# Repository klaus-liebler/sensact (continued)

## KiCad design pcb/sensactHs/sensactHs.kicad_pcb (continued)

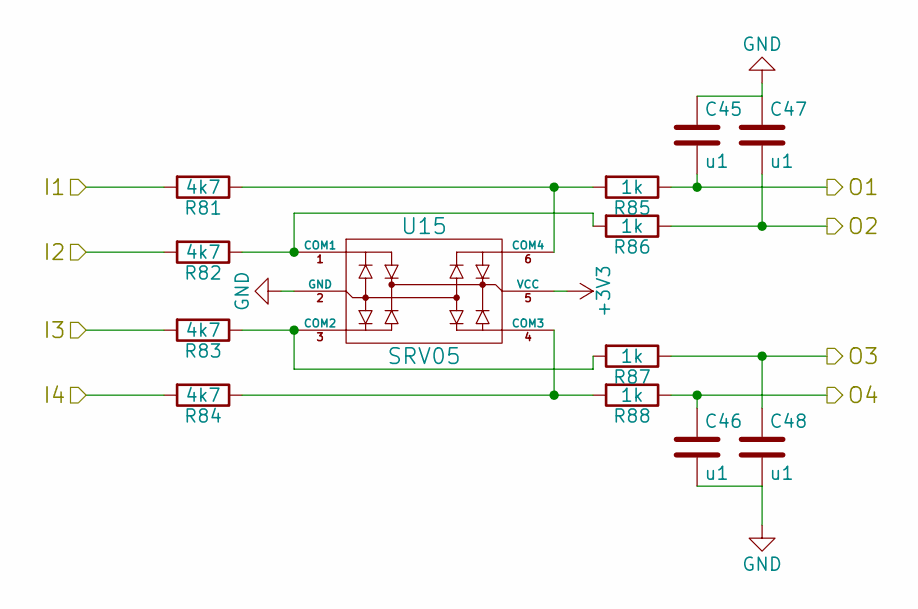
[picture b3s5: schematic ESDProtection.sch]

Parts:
C5, C6, C7, C8: u1; C_0805_HandSoldering
R1, R2, R3, R4: 4k7; R_0805_HandSoldering
R5, R6, R7, R8: 1k; R_0805_HandSoldering
U5: SRV05; SOT-23-6_handsolder

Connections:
/01 input/ESDProtection1/I1: R1.2; also elsewhere on the board
/01 input/ESDProtection1/I2: R2.2; also elsewhere on the board
/01 input/ESDProtection1/I3: R3.2; also elsewhere on the board
/01 input/ESDProtection1/I4: R4.2; also elsewhere on the board
/01 input/ESDProtection1/O1: C5.2, R5.1; also elsewhere on the board
/01 input/ESDProtection1/O2: C7.2, R6.1; also elsewhere on the board
/01 input/ESDProtection1/O3: C8.1, R7.1; also elsewhere on the board
/01 input/ESDProtection1/O4: C6.1, R8.1; also elsewhere on the board
GND: C5.1, C6.2, C7.1, C8.2, U5.2 (GND); also elsewhere on the board
unnamed: R1.1, R5.2, U5.6 (COM4)
unnamed: R2.1, R6.2, U5.1 (COM1)
unnamed: R3.1, R7.2, U5.3 (COM2)
unnamed: R4.1, R8.2, U5.4 (COM3)

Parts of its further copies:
C9, C10, C11, C12, C13, C14, C15, C16, C17, C18, C19, C20, C21, C22, C23, C24, C25, C26, C27, C28, C29, C30, C31, C32, C33, C34, C35, C36, C37, C38, C39, C40, C41, C42, C43, C44, C45, C46, C47, C48, C49, C50, C51, C52, C53, C54, C55, C56, C57, C58, C59, C60, C61, C62, C63, C64, C65, C66, C67, C68: u1; C_0805_HandSoldering
R9, R10, R11, R12, R17, R18, R19, R20, R25, R26, R27, R28, R33, R34, R35, R36, R41, R42, R43, R44, R49, R50, R51, R52, R57, R58, R59, R60, R65, R66, R67, R68, R73, R74, R75, R76, R81, R82, R83, R84, R89, R90, R91, R92, R97, R98, R99, R100, R105, R106, R107, R108, R113, R114, R115, R116, R121, R122, R123, R124: 4k7; R_0805_HandSoldering
R13, R14, R15, R16, R21, R22, R23, R24, R29, R30, R31, R32, R37, R38, R39, R40, R45, R46, R47, R48, R53, R54, R55, R56, R61, R62, R63, R64, R69, R70, R71, R72, R77, R78, R79, R80, R85, R86, R87, R88, R93, R94, R95, R96, R101, R102, R103, R104, R109, R110, R111, R112, R117, R118, R119, R120, R125, R126, R127, R128: 1k; R_0805_HandSoldering
U6, U7, U8, U9, U10, U11, U12, U13, U14, U15, U16, U17, U18, U19, U20: SRV05; SOT-23-6_handsolder

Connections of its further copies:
/01 input/ESDProtection2/I1: R9.2; also elsewhere on the board
/01 input/ESDProtection2/I2: R10.2; also elsewhere on the board
/01 input/ESDProtection2/I3: R11.2; also elsewhere on the board
/01 input/ESDProtection2/I4: R12.2; also elsewhere on the board
/01 input/ESDProtection2/O1: C9.2, R13.1; also elsewhere on the board
/01 input/ESDProtection2/O2: C11.2, R14.1; also elsewhere on the board
/01 input/ESDProtection2/O3: C12.1, R15.1; also elsewhere on the board
/01 input/ESDProtection2/O4: C10.1, R16.1; also elsewhere on the board
/01 input/ESDProtection3/I1: R17.2; also elsewhere on the board
/01 input/ESDProtection3/I2: R18.2; also elsewhere on the board
/01 input/ESDProtection3/I3: R19.2; also elsewhere on the board
/01 input/ESDProtection3/I4: R20.2; also elsewhere on the board
/01 input/ESDProtection3/O1: C13.2, R21.1; also elsewhere on the board
/01 input/ESDProtection3/O2: C15.2, R22.1; also elsewhere on the board
/01 input/ESDProtection3/O3: C16.1, R23.1; also elsewhere on the board
/01 input/ESDProtection3/O4: C14.1, R24.1; also elsewhere on the board
/01 input/ESDProtection4/I1: R25.2; also elsewhere on the board
/01 input/ESDProtection4/I2: R26.2; also elsewhere on the board
/01 input/ESDProtection4/I3: R27.2; also elsewhere on the board
/01 input/ESDProtection4/I4: R28.2; also elsewhere on the board
/01 input/ESDProtection4/O1: C17.2, R29.1; also elsewhere on the board
/01 input/ESDProtection4/O2: C19.2, R30.1; also elsewhere on the board
/01 input/ESDProtection4/O3: C20.1, R31.1; also elsewhere on the board
/01 input/ESDProtection4/O4: C18.1, R32.1; also elsewhere on the board
/01 input/ESDProtection5/I1: R33.2; also elsewhere on the board
/01 input/ESDProtection5/I2: R34.2; also elsewhere on the board
/01 input/ESDProtection5/I3: R35.2; also elsewhere on the board
/01 input/ESDProtection5/I4: R36.2; also elsewhere on the board
/01 input/ESDProtection5/O1: C21.2, R37.1; also elsewhere on the board
/01 input/ESDProtection5/O2: C23.2, R38.1; also elsewhere on the board
/01 input/ESDProtection5/O3: C24.1, R39.1; also elsewhere on the board
/01 input/ESDProtection5/O4: C22.1, R40.1; also elsewhere on the board
/01 input/ESDProtection6/I1: R41.2; also elsewhere on the board
/01 input/ESDProtection6/I2: R42.2; also elsewhere on the board
/01 input/ESDProtection6/I3: R43.2; also elsewhere on the board
/01 input/ESDProtection6/I4: R44.2; also elsewhere on the board
/01 input/ESDProtection6/O1: C25.2, R45.1; also elsewhere on the board
/01 input/ESDProtection6/O2: C27.2, R46.1; also elsewhere on the board
/01 input/ESDProtection6/O3: C28.1, R47.1; also elsewhere on the board
/01 input/ESDProtection6/O4: C26.1, R48.1; also elsewhere on the board
/01 input/ESDProtection7/I1: R49.2; also elsewhere on the board
/01 input/ESDProtection7/I2: R50.2; also elsewhere on the board
/01 input/ESDProtection7/I3: R51.2; also elsewhere on the board
/01 input/ESDProtection7/I4: R52.2; also elsewhere on the board
/01 input/ESDProtection7/O1: C29.2, R53.1; also elsewhere on the board
/01 input/ESDProtection7/O2: C31.2, R54.1; also elsewhere on the board
/01 input/ESDProtection7/O3: C32.1, R55.1; also elsewhere on the board
/01 input/ESDProtection7/O4: C30.1, R56.1; also elsewhere on the board
/01 input/ESDProtection8/I1: R57.2; also elsewhere on the board
/01 input/ESDProtection8/I2: R58.2; also elsewhere on the board
/01 input/ESDProtection8/I3: R59.2; also elsewhere on the board
/01 input/ESDProtection8/I4: R60.2; also elsewhere on the board
/01 input/ESDProtection8/O1: C33.2, R61.1; also elsewhere on the board
/01 input/ESDProtection8/O2: C35.2, R62.1; also elsewhere on the board
/01 input/ESDProtection8/O3: C36.1, R63.1; also elsewhere on the board
/01 input/ESDProtection8/O4: C34.1, R64.1; also elsewhere on the board
/01 input/ESDProtection9/I1: R65.2; also elsewhere on the board
/01 input/ESDProtection9/I2: R66.2; also elsewhere on the board
/01 input/ESDProtection9/I3: R67.2; also elsewhere on the board
/01 input/ESDProtection9/I4: R68.2; also elsewhere on the board
/01 input/ESDProtection9/O1: C37.2, R69.1; also elsewhere on the board
/01 input/ESDProtection9/O2: C39.2, R70.1; also elsewhere on the board
/01 input/ESDProtection9/O3: C40.1, R71.1; also elsewhere on the board
/01 input/ESDProtection9/O4: C38.1, R72.1; also elsewhere on the board
/01 input/ESDProtection10/I1: R73.2; also elsewhere on the board
/01 input/ESDProtection10/I2: R74.2; also elsewhere on the board
/01 input/ESDProtection10/I3: R75.2; also elsewhere on the board
/01 input/ESDProtection10/I4: R76.2; also elsewhere on the board
/01 input/ESDProtection10/O1: C41.2, R77.1; also elsewhere on the board
/01 input/ESDProtection10/O2: C43.2, R78.1; also elsewhere on the board
/01 input/ESDProtection10/O3: C44.1, R79.1; also elsewhere on the board
/01 input/ESDProtection10/O4: C42.1, R80.1; also elsewhere on the board
/01 input/ESDProtection11/I1: R81.2; also elsewhere on the board
/01 input/ESDProtection11/I2: R82.2; also elsewhere on the board
/01 input/ESDProtection11/I3: R83.2; also elsewhere on the board
/01 input/ESDProtection11/I4: R84.2; also elsewhere on the board
/01 input/ESDProtection11/O1: C45.2, R85.1; also elsewhere on the board
/01 input/ESDProtection11/O2: C47.2, R86.1; also elsewhere on the board
/01 input/ESDProtection11/O3: C48.1, R87.1; also elsewhere on the board
/01 input/ESDProtection11/O4: C46.1, R88.1; also elsewhere on the board
/01 input/ESDProtection12/I1: R89.2; also elsewhere on the board
/01 input/ESDProtection12/I2: R90.2; also elsewhere on the board
/01 input/ESDProtection12/I3: R91.2; also elsewhere on the board
/01 input/ESDProtection12/I4: R92.2; also elsewhere on the board
/01 input/ESDProtection12/O1: C49.2, R93.1; also elsewhere on the board
/01 input/ESDProtection12/O2: C51.2, R94.1; also elsewhere on the board
/01 input/ESDProtection12/O3: C52.1, R95.1; also elsewhere on the board
/01 input/ESDProtection12/O4: C50.1, R96.1; also elsewhere on the board
/01 input/ESDProtection13/I1: R97.2; also elsewhere on the board
/01 input/ESDProtection13/I2: R98.2; also elsewhere on the board
/01 input/ESDProtection13/I3: R99.2; also elsewhere on the board
/01 input/ESDProtection13/I4: R100.2; also elsewhere on the board
/01 input/ESDProtection13/O1: C53.2, R101.1; also elsewhere on the board
/01 input/ESDProtection13/O2: C55.2, R102.1; also elsewhere on the board
/01 input/ESDProtection13/O3: C56.1, R103.1; also elsewhere on the board
/01 input/ESDProtection13/O4: C54.1, R104.1; also elsewhere on the board
/01 input/ESDProtection14/I1: R105.2; also elsewhere on the board
/01 input/ESDProtection14/I2: R106.2; also elsewhere on the board
/01 input/ESDProtection14/I3: R107.2; also elsewhere on the board
/01 input/ESDProtection14/I4: R108.2; also elsewhere on the board
/01 input/ESDProtection14/O1: C57.2, R109.1; also elsewhere on the board
/01 input/ESDProtection14/O2: C59.2, R110.1; also elsewhere on the board
/01 input/ESDProtection14/O3: C60.1, R111.1; also elsewhere on the board
/01 input/ESDProtection14/O4: C58.1, R112.1; also elsewhere on the board
/01 input/ESDProtection15/I1: R113.2; also elsewhere on the board
/01 input/ESDProtection15/I2: R114.2; also elsewhere on the board
/01 input/ESDProtection15/I3: R115.2; also elsewhere on the board
/01 input/ESDProtection15/I4: R116.2; also elsewhere on the board
/01 input/ESDProtection15/O1: C61.2, R117.1; also elsewhere on the board
/01 input/ESDProtection15/O2: C63.2, R118.1; also elsewhere on the board
/01 input/ESDProtection15/O3: C64.1, R119.1; also elsewhere on the board
/01 input/ESDProtection15/O4: C62.1, R120.1; also elsewhere on the board
/01 input/ESDProtection16/I1: R121.2; also elsewhere on the board
/01 input/ESDProtection16/I2: R122.2; also elsewhere on the board
/01 input/ESDProtection16/I3: R123.2; also elsewhere on the board
/01 input/ESDProtection16/I4: R124.2; also elsewhere on the board
/01 input/ESDProtection16/O1: C65.2, R125.1; also elsewhere on the board
/01 input/ESDProtection16/O2: C67.2, R126.1; also elsewhere on the board
/01 input/ESDProtection16/O3: C68.1, R127.1; also elsewhere on the board
/01 input/ESDProtection16/O4: C66.1, R128.1; also elsewhere on the board
GND: C9.1, C10.2, C11.1, C12.2, C13.1, C14.2, C15.1, C16.2, C17.1, C18.2, C19.1, C20.2, C21.1, C22.2, C23.1, C24.2, C25.1, C26.2, C27.1, C28.2, C29.1, C30.2, C31.1, C32.2, C33.1, C34.2, C35.1, C36.2, C37.1, C38.2, C39.1, C40.2, C41.1, C42.2, C43.1, C44.2, C45.1, C46.2, C47.1, C48.2, C49.1, C50.2, C51.1, C52.2, C53.1, C54.2, C55.1, C56.2, C57.1, C58.2, C59.1, C60.2, C61.1, C62.2, C63.1, C64.2, C65.1, C66.2, C67.1, C68.2, U6.2 (GND), U7.2 (GND), U8.2 (GND), U9.2 (GND), U10.2 (GND), U11.2 (GND), U12.2 (GND), U13.2 (GND), U14.2 (GND), U15.2 (GND), U16.2 (GND), U17.2 (GND), U18.2 (GND), U19.2 (GND), U20.2 (GND); also elsewhere on the board
unnamed: R10.1, R14.2, U6.1 (COM1)
unnamed: R11.1, R15.2, U6.3 (COM2)
unnamed: R12.1, R16.2, U6.4 (COM3)
unnamed: R9.1, R13.2, U6.6 (COM4)
unnamed: R17.1, R21.2, U7.6 (COM4)
unnamed: R18.1, R22.2, U7.1 (COM1)
unnamed: R19.1, R23.2, U7.3 (COM2)
unnamed: R20.1, R24.2, U7.4 (COM3)
unnamed: R25.1, R29.2, U8.6 (COM4)
unnamed: R26.1, R30.2, U8.1 (COM1)
unnamed: R27.1, R31.2, U8.3 (COM2)
unnamed: R28.1, R32.2, U8.4 (COM3)
unnamed: R33.1, R37.2, U9.6 (COM4)
unnamed: R34.1, R38.2, U9.1 (COM1)
unnamed: R35.1, R39.2, U9.3 (COM2)
unnamed: R36.1, R40.2, U9.4 (COM3)
unnamed: R41.1, R45.2, U10.6 (COM4)
unnamed: R42.1, R46.2, U10.1 (COM1)
unnamed: R43.1, R47.2, U10.3 (COM2)
unnamed: R44.1, R48.2, U10.4 (COM3)
unnamed: R49.1, R53.2, U11.6 (COM4)
unnamed: R50.1, R54.2, U11.1 (COM1)
unnamed: R51.1, R55.2, U11.3 (COM2)
unnamed: R52.1, R56.2, U11.4 (COM3)
unnamed: R57.1, R61.2, U12.6 (COM4)
unnamed: R58.1, R62.2, U12.1 (COM1)
unnamed: R59.1, R63.2, U12.3 (COM2)
unnamed: R60.1, R64.2, U12.4 (COM3)
unnamed: R65.1, R69.2, U13.6 (COM4)
unnamed: R66.1, R70.2, U13.1 (COM1)
unnamed: R67.1, R71.2, U13.3 (COM2)
unnamed: R68.1, R72.2, U13.4 (COM3)
unnamed: R73.1, R77.2, U14.6 (COM4)
unnamed: R74.1, R78.2, U14.1 (COM1)
unnamed: R75.1, R79.2, U14.3 (COM2)
unnamed: R76.1, R80.2, U14.4 (COM3)
unnamed: R81.1, R85.2, U15.6 (COM4)
unnamed: R82.1, R86.2, U15.1 (COM1)
unnamed: R83.1, R87.2, U15.3 (COM2)
unnamed: R84.1, R88.2, U15.4 (COM3)
unnamed: R89.1, R93.2, U16.6 (COM4)
unnamed: R90.1, R94.2, U16.1 (COM1)
unnamed: R91.1, R95.2, U16.3 (COM2)
unnamed: R92.1, R96.2, U16.4 (COM3)
unnamed: R100.1, R104.2, U17.4 (COM3)
unnamed: R97.1, R101.2, U17.6 (COM4)
unnamed: R98.1, R102.2, U17.1 (COM1)
unnamed: R99.1, R103.2, U17.3 (COM2)
unnamed: R105.1, R109.2, U18.6 (COM4)
unnamed: R106.1, R110.2, U18.1 (COM1)
unnamed: R107.1, R111.2, U18.3 (COM2)
unnamed: R108.1, R112.2, U18.4 (COM3)
unnamed: R113.1, R117.2, U19.6 (COM4)
unnamed: R114.1, R118.2, U19.1 (COM1)
unnamed: R115.1, R119.2, U19.3 (COM2)
unnamed: R116.1, R120.2, U19.4 (COM3)
unnamed: R121.1, R125.2, U20.6 (COM4)
unnamed: R122.1, R126.2, U20.1 (COM1)
unnamed: R123.1, R127.2, U20.3 (COM2)
unnamed: R124.1, R128.2, U20.4 (COM3)

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
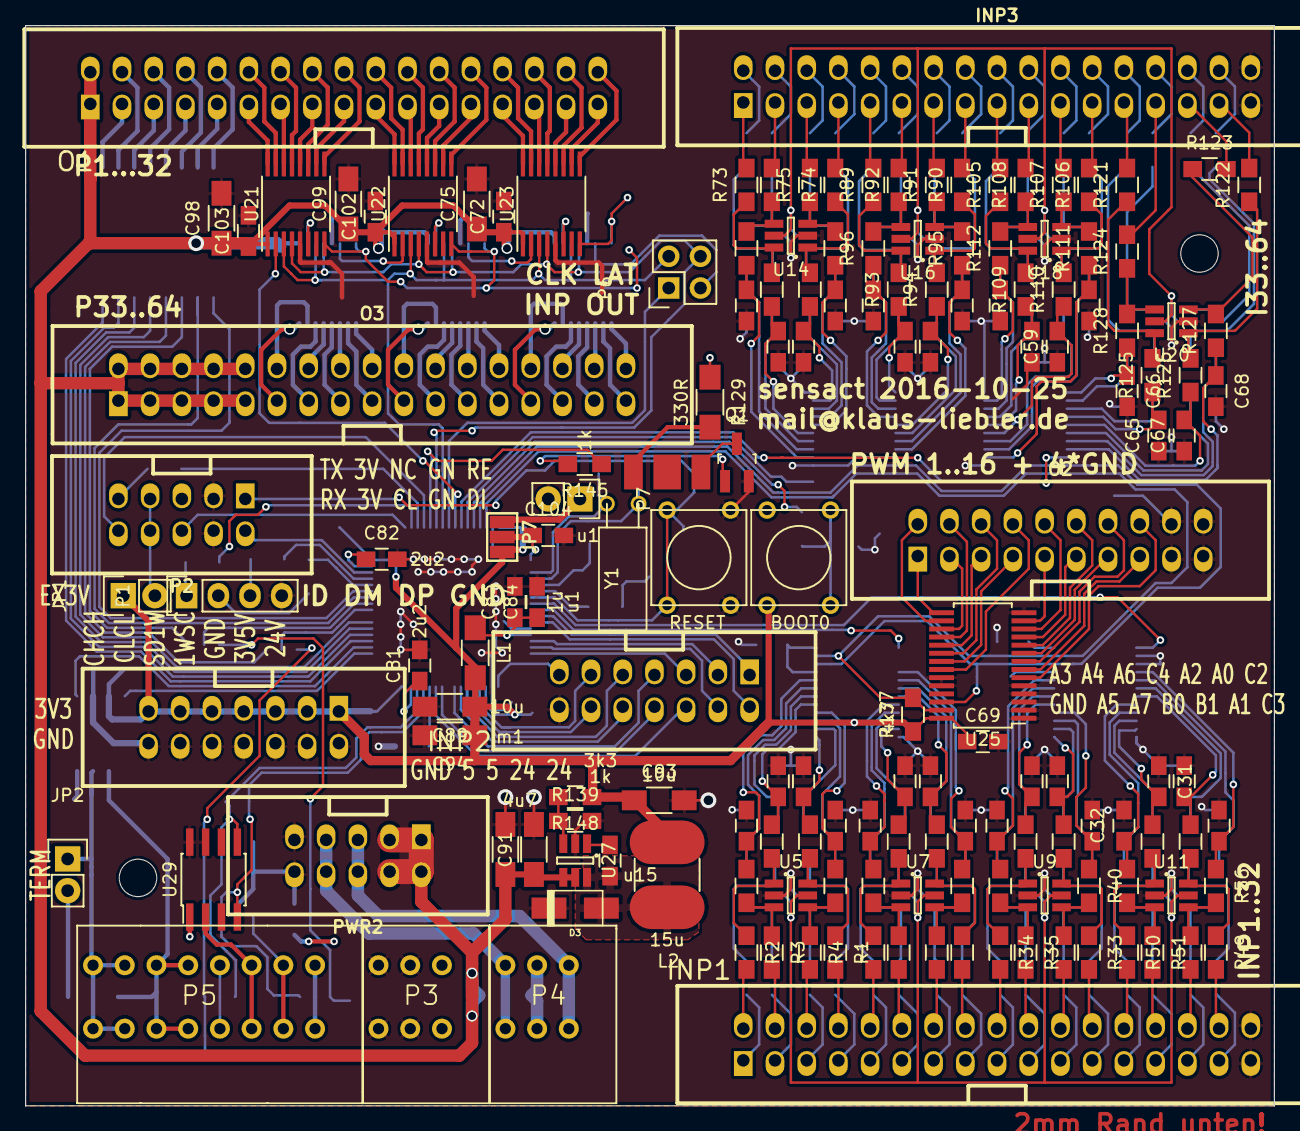
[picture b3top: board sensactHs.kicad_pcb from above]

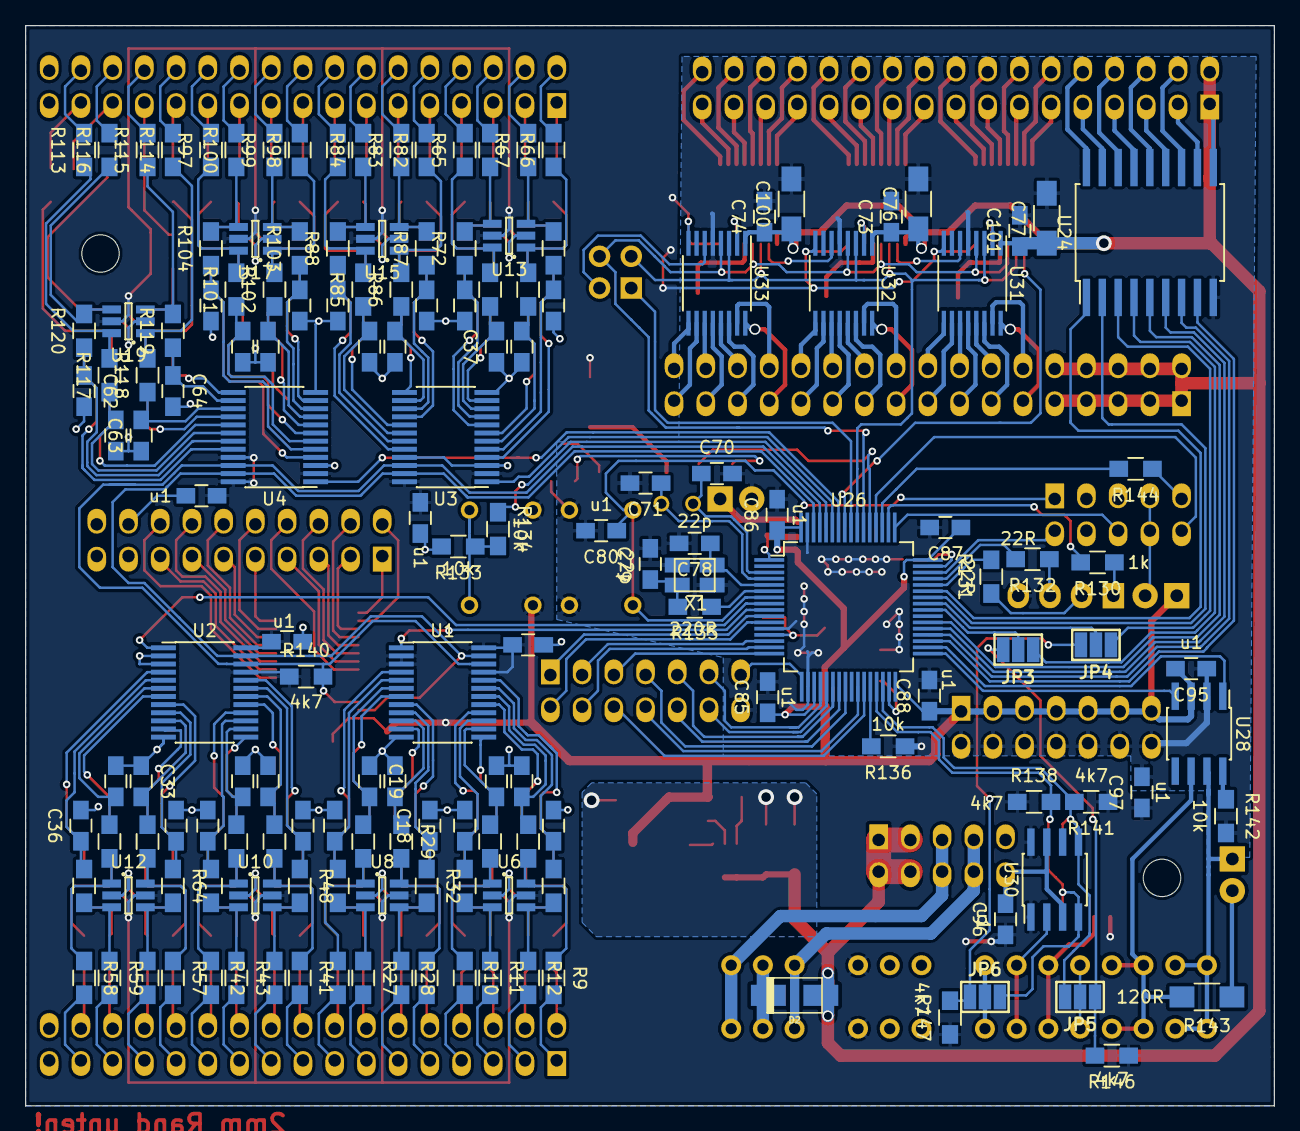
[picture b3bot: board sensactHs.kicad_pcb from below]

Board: 2 copper layers, 100.0 x 86.5 mm, 319 parts (158 on the bottom side), 356 nets.

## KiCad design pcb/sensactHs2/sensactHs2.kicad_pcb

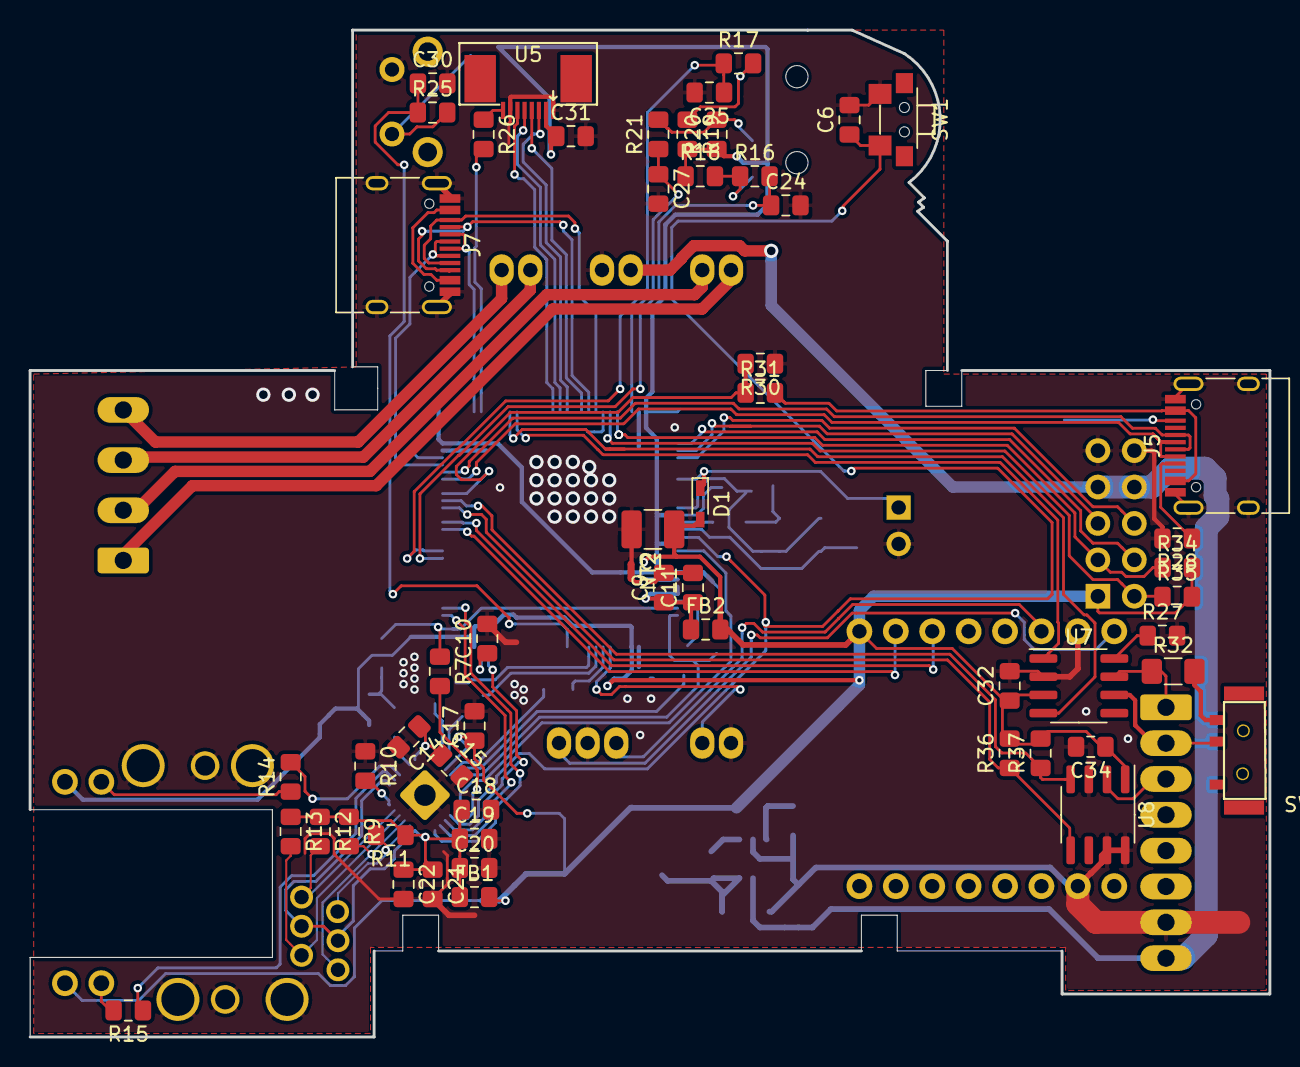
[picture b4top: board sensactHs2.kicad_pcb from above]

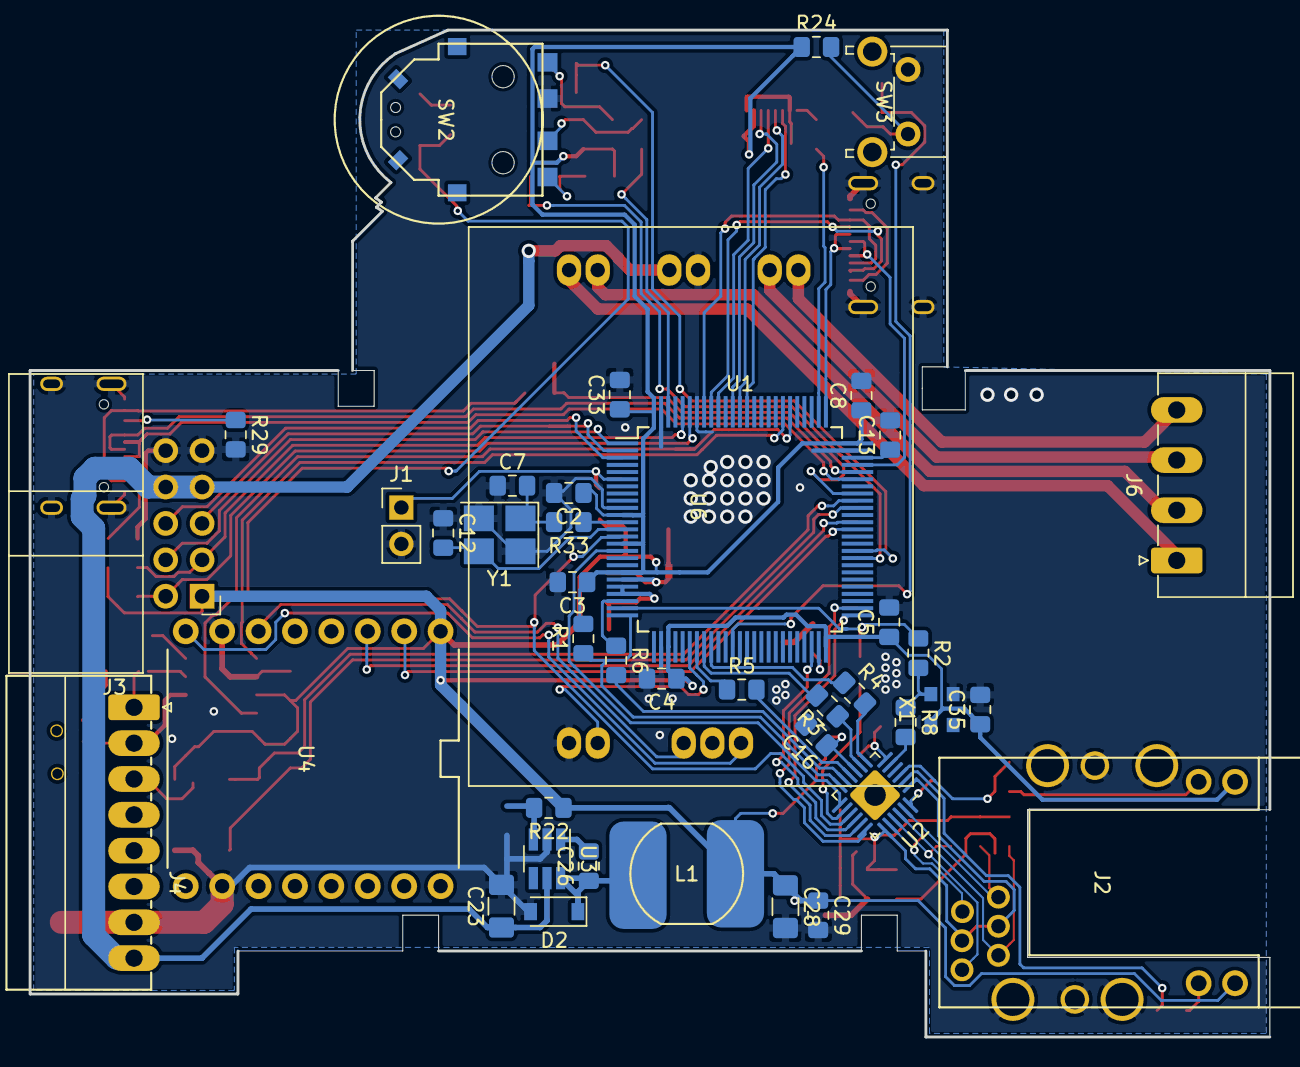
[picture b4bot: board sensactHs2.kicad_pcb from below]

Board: 2 copper layers, 86.5 x 70.2 mm, 98 parts (42 on the bottom side), 91 nets.

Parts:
C1: 10u; C_1210_3225Metric_Pad1.42x2.65mm_HandSolder
C2, C3, C4, C5, C6, C8, C11, C14, C16, C18, C19, C24, C25, C26, C27, C29, C30, C31, C32, C33, C34, C35: u1; C_0805_2012Metric_Pad1.15x1.40mm_HandSolder
C7, C12: 22p; C_0805_2012Metric_Pad1.15x1.40mm_HandSolder
C9: 1u; C_0805_2012Metric_Pad1.15x1.40mm_HandSolder
C10, C13, C15, C17, C20: 2u2; C_0805_2012Metric_Pad1.15x1.40mm_HandSolder
C21, C22: 10n; C_0805_2012Metric_Pad1.15x1.40mm_HandSolder
C23: 4u7; C_1206_3216Metric_Pad1.42x1.75mm_HandSolder
C28: m1; C_1206_3216Metric_Pad1.42x1.75mm_HandSolder
D1: D; D_SC-80_HandSoldering
D2: MBR0540; D_SOD-123
FB1: Ferrite_Bead_Small; L_0805_2012Metric_Pad1.15x1.40mm_HandSolder
FB2: Ferrite_Bead_Small; R_0805_2012Metric_Pad1.15x1.40mm_HandSolder
J1: BACKUP; PinHeader_1x02_P2.54mm_Vertical
J2: dr-mag-l834-1g1t-91; L834-1G1T-91
J3: SensactBusConnector; IDC-Header_2x05_P2.54mm_Horizontal
J4: UNIVERSAL; PhoenixContact_MC_0,5_8-G-2.5_1x08_P2.50mm_Horizontal
J5: USB; USB_C_Receptacle_HRO_TYPE-C-31-M-12
J6: SPEAKER; PhoenixContact_MC_1,5_4-G-3.5_1x04_P3.50mm_Horizontal
J7: PROG; USB_C_Receptacle_HRO_TYPE-C-31-M-12
L1: 150u; Inductor_CD75_handsolder
NT2: Net-Tie_2; NetTie-2_SMD_Pad0.5mm
R1: 1K5; R_0805_2012Metric_Pad1.15x1.40mm_HandSolder
R2, R3, R4, R5, R6, R7, R8: 33R; R_0805_2012Metric_Pad1.15x1.40mm_HandSolder
R9, R11, R12, R13: 49R; R_0805_2012Metric_Pad1.15x1.40mm_HandSolder
R10: 12K1; R_0805_2012Metric_Pad1.15x1.40mm_HandSolder
R14, R15: K33; R_0805_2012Metric_Pad1.15x1.40mm_HandSolder
R16, R17, R18, R19, R20, R21, R24, R25: 1k; R_0805_2012Metric_Pad1.15x1.40mm_HandSolder
R22, R30: 3k3; R_0805_2012Metric_Pad1.15x1.40mm_HandSolder
R26: 10R; R_0805_2012Metric_Pad1.15x1.40mm_HandSolder
R27: 10k; R_0805_2012Metric_Pad1.15x1.40mm_HandSolder
R28, R29: 5k1; R_0805_2012Metric_Pad1.15x1.40mm_HandSolder
R31, R34, R35, R36, R37: 2k2; R_0805_2012Metric_Pad1.15x1.40mm_HandSolder
R32: R12; R_1206_3216Metric_Pad1.42x1.75mm_HandSolder
R33: R; R_0805_2012Metric_Pad1.15x1.40mm_HandSolder
SW1: SW_Push; SW_SPST_2x4x3,5
SW2: Mitsumi_SIQ-02FVS3
SW3: SW_Push; SW_Tactile_SPST_Angled_PTS645Vx83-2LFS
SW4: SW_Push_SPDT; MSK12C02
U1: STM32F407VETx; LQFP-100_14x14mm_Pitch0.5mm_hnadsolder
U2: LAN8720A; QFN-24-1EP_4x4mm_P0.5mm_EP2.6x2.6mm_handsolder
U3: LMR14206; SOT-23-6_Handsoldering
U4: DFPlayerMini
U5: FP-096H09A; FPC_TOP_1x08-1MP_P0.50mm_Horizontal
U6: MODULE_TPA3110stereo; MODULE_TPA3110stereo_woScrewa
U7: SN65HVD230; SOIC-8_3.9x4.9mm_P1.27mm
U8: DS2482-100; SOIC-8_3.9x4.9mm_P1.27mm
X1: XO32; Oscillator_SMD_EuroQuartz_XO32-4Pin_3.2x2.5mm
Y1: Crystal_GND24; Crystal_SMD_3225-4Pin_3.2x2.5mm_HandSoldering

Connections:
+3.3VA: C9.1, C11.1, FB2.1, U1.21, U1.22
+3V3: C1.1, C2.1, C3.1, C4.1, C5.1, C8.1, C16.1, C17.1, C28.1, C29.1, C31.1, C32.1, C33.1, C34.1, C35.1, D1.2, FB1.2, FB2.2, J2.14, J2.16, J3.1, L1.1, R1.2, R18.1, R19.2, R20.1, R22.1, R24.1, R34.2, R35.2, R36.2, R37.2, U1.11, U1.15, U1.19, U1.28, U1.50, U1.75, U1.100, U2.9, U4.1, U5.2, U7.3, U8.1, X1.4
+24V: C23.1, J3.7, J3.8, J4.8, U3.5, U6.9
/eth/LED1: R14.2, U2.3
/eth/LED2: R15.1, U2.2
/eth/RX_N: J2.6, R13.2, U2.22
/eth/RX_P: J2.4, R12.2, U2.23
/eth/TX_N: J2.10, R11.2, U2.20
/eth/TX_P: J2.12, R9.2, U2.21
/eth/VDD2A: C18.1, C19.1, C20.1, C21.1, C22.1, FB1.1, J2.5, J2.11, R9.1, R11.1, R12.1, R13.1, U2.1, U2.19
/io/1wire: J4.3, U8.2
/io/CANH: J4.1, R32.1, U7.7
/io/CANL: J4.2, SW4.2, U7.6
/io/CB: C26.2, U3.1
/io/SW: C26.1, D2.1, L1.2, U3.6
CANR: U1.81, U7.4
CANT: U1.82, U7.1
ETH_CLK: R2.1, R7.1, U1.24
ETH_CRS: R6.1, U1.23
ETH_MDC: U1.16, U2.13
ETH_MDIO: R1.1, U1.25, U2.12
ETH_RX0: R3.2, U1.33
ETH_RX1: R4.1, U1.34
ETH_RXER: R5.1, U1.32
ETH_TX0: U1.51, U2.17
ETH_TX1: U1.52, U2.18
ETH_TXEN: U1.48, U2.16
GND: C1.2, C2.2, C3.2, C4.2, C5.2, C6.2, C7.1, C8.2, C10.2, C12.1, C13.2, C14.2, C15.2, C16.2, C17.2, C18.2, C19.2, C20.2, C21.2, C22.2, C23.2, C24.2, C25.2, C27.2, C28.2, C29.2, C30.2, C31.2, C32.2, C33.2, C34.2, C35.2, D2.2, J1.2, J2.SH, J3.9, J3.10, J4.7, J5.A1, J5.A12, J5.B1, J5.B12, J5.S1, J7.A1, J7.A12, J7.B1, J7.B12, J7.S1, NT2.1, R10.1, R27.2, R28.2, R29.2, R30.1, SW1.1, SW2.C, SW3.1, U1.10, U1.27, U1.74, U1.94, U1.99, U2.25, U3.2, U4.7, U4.10, U5.1, U5.7, U6.1, U6.4, U6.8, U7.2, U8.3, U8.7, U8.8, X1.2, Y1.2, Y1.4
GNDA: C9.2, C11.2, NT2.2, U1.20
INT0: J3.4, U1.1
INT1: J3.5, U1.2
INT2: J3.6, U1.3
LCD_BL: R26.2, U1.77
LCD_MOSI: U1.91, U5.4
LCD_RS: U1.88, U5.5
LCD_RST: U1.87, U5.6
LCD_SCK: U1.89, U5.3
MP3_MRX: U1.64, U4.3
MP3_MTX: U1.63, U4.2
MP3_MUTE: U1.31, U6.2
NRST: C6.1, SW1.2, U1.14, U2.15
unnamed: C7.2, R33.2, Y1.1
unnamed: C10.1, U1.49
unnamed: C12.2, U1.13, Y1.3
unnamed: C13.1, U1.73
unnamed: C14.1, C15.1, U2.6
unnamed: D1.1, J1.1, U1.6
unnamed: J2.13, R14.1
unnamed: J2.15, R15.2
unnamed: J5.A4, J5.A9, J5.B4, J5.B9, R31.2
unnamed: J5.A5, R28.1
unnamed: J5.B5, R29.1
unnamed: J6.1, U6.11
unnamed: J6.2, U6.10
unnamed: J6.3, U6.7
unnamed: J6.4, U6.6
unnamed: J7.A4, J7.A9, J7.B4, J7.B9
unnamed: R2.2, R8.1, X1.3
unnamed: R3.1, U2.8
unnamed: R4.2, U2.7
unnamed: R5.2, U2.10
unnamed: R6.2, U2.11
unnamed: R7.2, U2.14
unnamed: R8.2, U2.5
unnamed: R10.2, U2.24
unnamed: R16.1, R18.2, SW2.A
unnamed: R17.2, R19.1, SW2.B
unnamed: R20.2, R21.2, SW2.S
unnamed: R22.2, U3.3
unnamed: R24.2, R25.2, SW3.2
unnamed: R26.1, U5.8
unnamed: R27.1, U7.8
unnamed: R32.2, SW4.3
unnamed: R33.1, U1.12
unnamed: U4.6, U6.3
unnamed: U4.8, U6.5
ROT_A: C24.1, R16.2, U1.59
ROT_B: C25.1, R17.1, U1.60
ROT_S: C27.1, R21.1, U1.98
RX1: J7.A8, J7.B8, U1.93
SCL1: J3.2, R35.1, U1.95
SCL2: R37.1, U1.67, U8.4
SDA1: J3.3, R34.1, U1.96
SDA2: R36.1, U1.66, U8.5
SWCLK: J7.A7, J7.B7, U1.76
SWDIO: J7.A6, J7.B6, U1.72
SWITCH: C30.1, R25.1, U1.37
TX1: J7.A5, J7.B5, U1.92
USB+: J5.A6, J5.B6, U1.71
USB-: J5.A7, J5.B7, U1.70
VBUS: R30.2, R31.1, U1.68

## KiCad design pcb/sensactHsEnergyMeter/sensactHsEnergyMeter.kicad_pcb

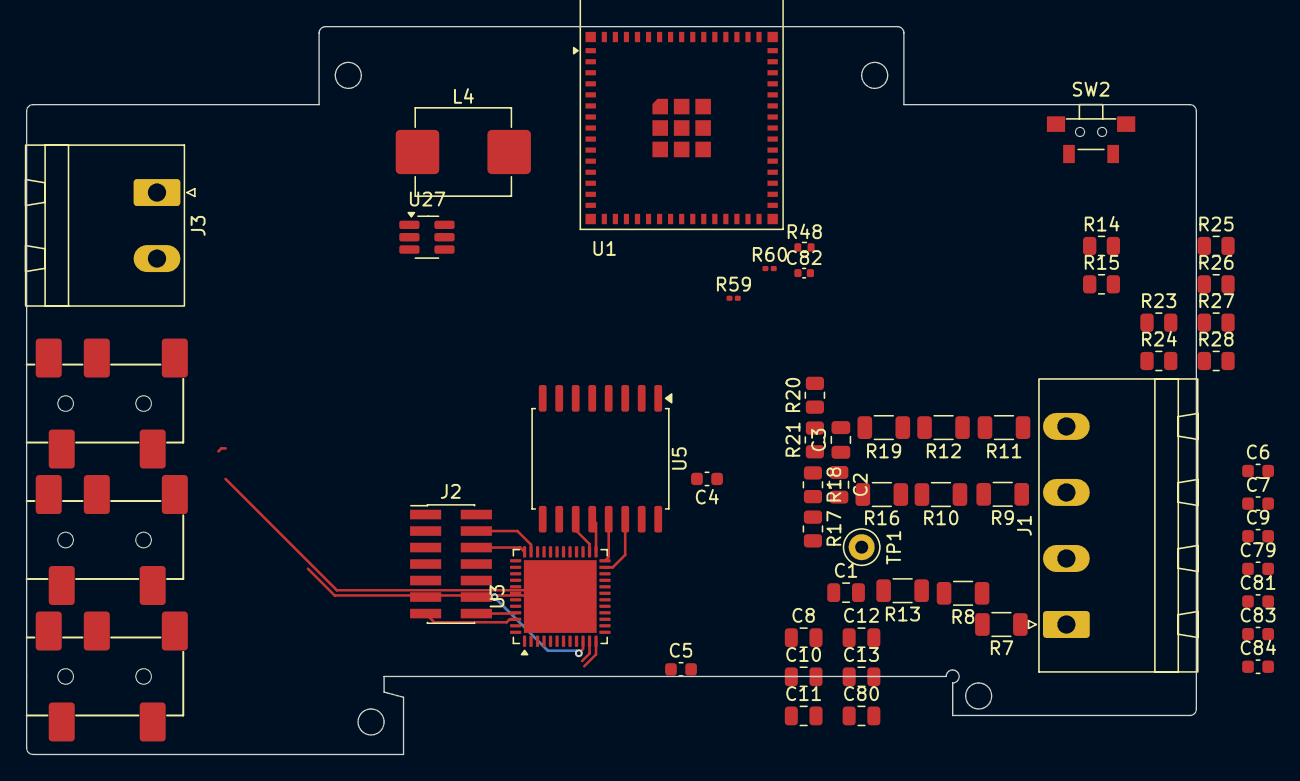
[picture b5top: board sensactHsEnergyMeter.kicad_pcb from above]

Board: 2 copper layers, 90.0 x 56.0 mm, 56 parts (0 on the bottom side), 36 nets.

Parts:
C1, C2, C3: 10n; C_0805_2012Metric
C4, C5, C6, C7, C9: u1; C_0603_1608Metric
C8, C10, C11, C12, C13: 22u; C_0805_2012Metric
C79: u1/35V; C_0603_1608Metric
C80: 10u/35V; C_0805_2012Metric
C81: u1/16V; C_0603_1608Metric
C82: 56p; C_0402_1005Metric
C83, C84: 22u; C_0603_1608Metric
J1: 230V; PhoenixContact_MSTBA_2,5_4-G-5,08_1x04_P5.08mm_Horizontal
J2: Conn_ST_STDC14; PinHeader_2x07_P1.27mm_Vertical_SMD
J3: 24V in; PhoenixContact_MSTBA_2,5_2-G-5,08_1x02_P5.08mm_Horizontal
J16, J17, J18: Headphones; PJ-327A
L4: 10uH; L_0630
R7, R8, R9, R10, R11, R12, R13, R16, R19: 1M; R_1206_3216Metric
R14, R15, R17, R18, R20, R21, R23, R24, R25, R26, R27, R28: 20k; R_0805_2012Metric
R48: 3k3; R_0402_1005Metric
R59: M1; R_0201_0603Metric
R60: 10k; R_0201_0603Metric
SW2: SW_Push_with_case; Button_2x4x3,5_handsolder
TP1: TestPoint; TestPoint_Keystone_5000-5004_Miniature
U1: ESP32-S3-MINI-1; ESP32-S2-MINI-1
U3: STM32G0B1CBUx; QFN-48-1EP_7x7mm_P0.5mm_EP5.6x5.6mm
U5: CA-IS3641HW; SOIC-16W_7.5x10.3mm_P1.27mm
U27: TPS54202DDC; SOT-23-6_Handsoldering

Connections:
5V_PD: C82.2, C83.1, C84.1, L4.1, R59.1
+3.3VADC: C4.1, C5.1, C7.2, C8.2, J2.3 (VCC), R14.2, R17.2, R20.2, R24.1, R26.1, R28.1, U3.4 (VBAT), U3.6 (VDD), U5.16 (VDD2)
+3V3: C9.2, C10.2, U5.1 (VDD1)
+24V: C79.2, C80.2, J3.1, U27.3 (VIN)
/ADC7: U3.18 (PA7), U3.19 (PB0), U3.20 (PB1), U3.21 (PB2), U3.22 (PB10)
/BOOT: C81.1, U27.6 (BOOT)
/DEBUG_RX: J2.13 (VCP_RX), U3.46 (PB7)
/DEBUG_TX: J2.14 (VCP_TX), U3.45 (PB6)
/FB: C82.1, R59.2, R60.2, U27.4 (FB)
/L1_230V: J1.1, R7.1
/L1_ADC: C1.2, R13.2, R14.1, R15.2, TP1.1 (1_1)
/L2_230V: J1.2, R9.1
/L2_ADC: C2.2, R16.2, R17.1, R18.2
/L3_230V: J1.3, R11.1
/L3_ADC: C3.2, R19.2, R20.1, R21.2
/MISO_ISO: U3.26 (PB14), U5.11 (VID)
/MOSI_ISO: U3.23 (PB11), U5.14 (VOA)
/NSS_ISO: U3.24 (PB12), U5.13 (VOB)
/RST: C6.1, J2.12 (~RST), SW2.2, U3.10 (PF2)
/SCK_ISO: U3.25 (PB13), U5.12 (VOC)
/SW: C81.2, L4.2, U27.2 (SW)
/SWCLK: J2.6 (JCLK/SWCLK), U3.36 (PA14)
/SWDIO: J2.4 (JTMS/SWDIO), U3.35 (PA13)
GND: C79.1, C80.1, C83.2, C84.2, J3.2, R48.1, U5.2 (GND1), U5.8 (GND1), U27.1 (GND)
GNDA: C1.1, C2.1, C3.1, C4.2, C5.2, C6.2, C7.1, C8.1, C9.1, C10.1, C11.2, C12.2, C13.2, J1.4, J2.5 (GND), J2.7 (GND), J2.11 (GNDDetect), R15.1, R18.1, R21.1, R23.1, R25.1, R27.1, SW2.1, SW2.MP, U3.7 (VSS), U3.49 (VSS), U5.9 (GND2), U5.10 (SEL), U5.15 (GND2)
unnamed: C11.1, J16.S, R23.2, R24.2
unnamed: C12.1, J17.S, R25.2, R26.2
unnamed: C13.1, J18.S, R27.2, R28.2
unnamed: R7.2, R8.1
unnamed: R9.2, R10.1
unnamed: R10.2, R16.1
unnamed: R11.2, R12.1
unnamed: R12.2, R19.1
unnamed: R8.2, R13.1
unnamed: R48.2, R60.1
unnamed: U1.1 (GND), U1.2 (GND), U1.42 (GND), U1.43 (GND), U1.46 (GND), U1.47 (GND), U1.48 (GND), U1.49 (GND), U1.50 (GND), U1.51 (GND), U1.52 (GND), U1.53 (GND), U1.54 (GND), U1.55 (GND), U1.56 (GND), U1.57 (GND), U1.58 (GND), U1.59 (GND), U1.60 (GND), U1.61 (GND), U1.62 (GND), U1.63 (GND), U1.64 (GND), U1.65 (GND)
